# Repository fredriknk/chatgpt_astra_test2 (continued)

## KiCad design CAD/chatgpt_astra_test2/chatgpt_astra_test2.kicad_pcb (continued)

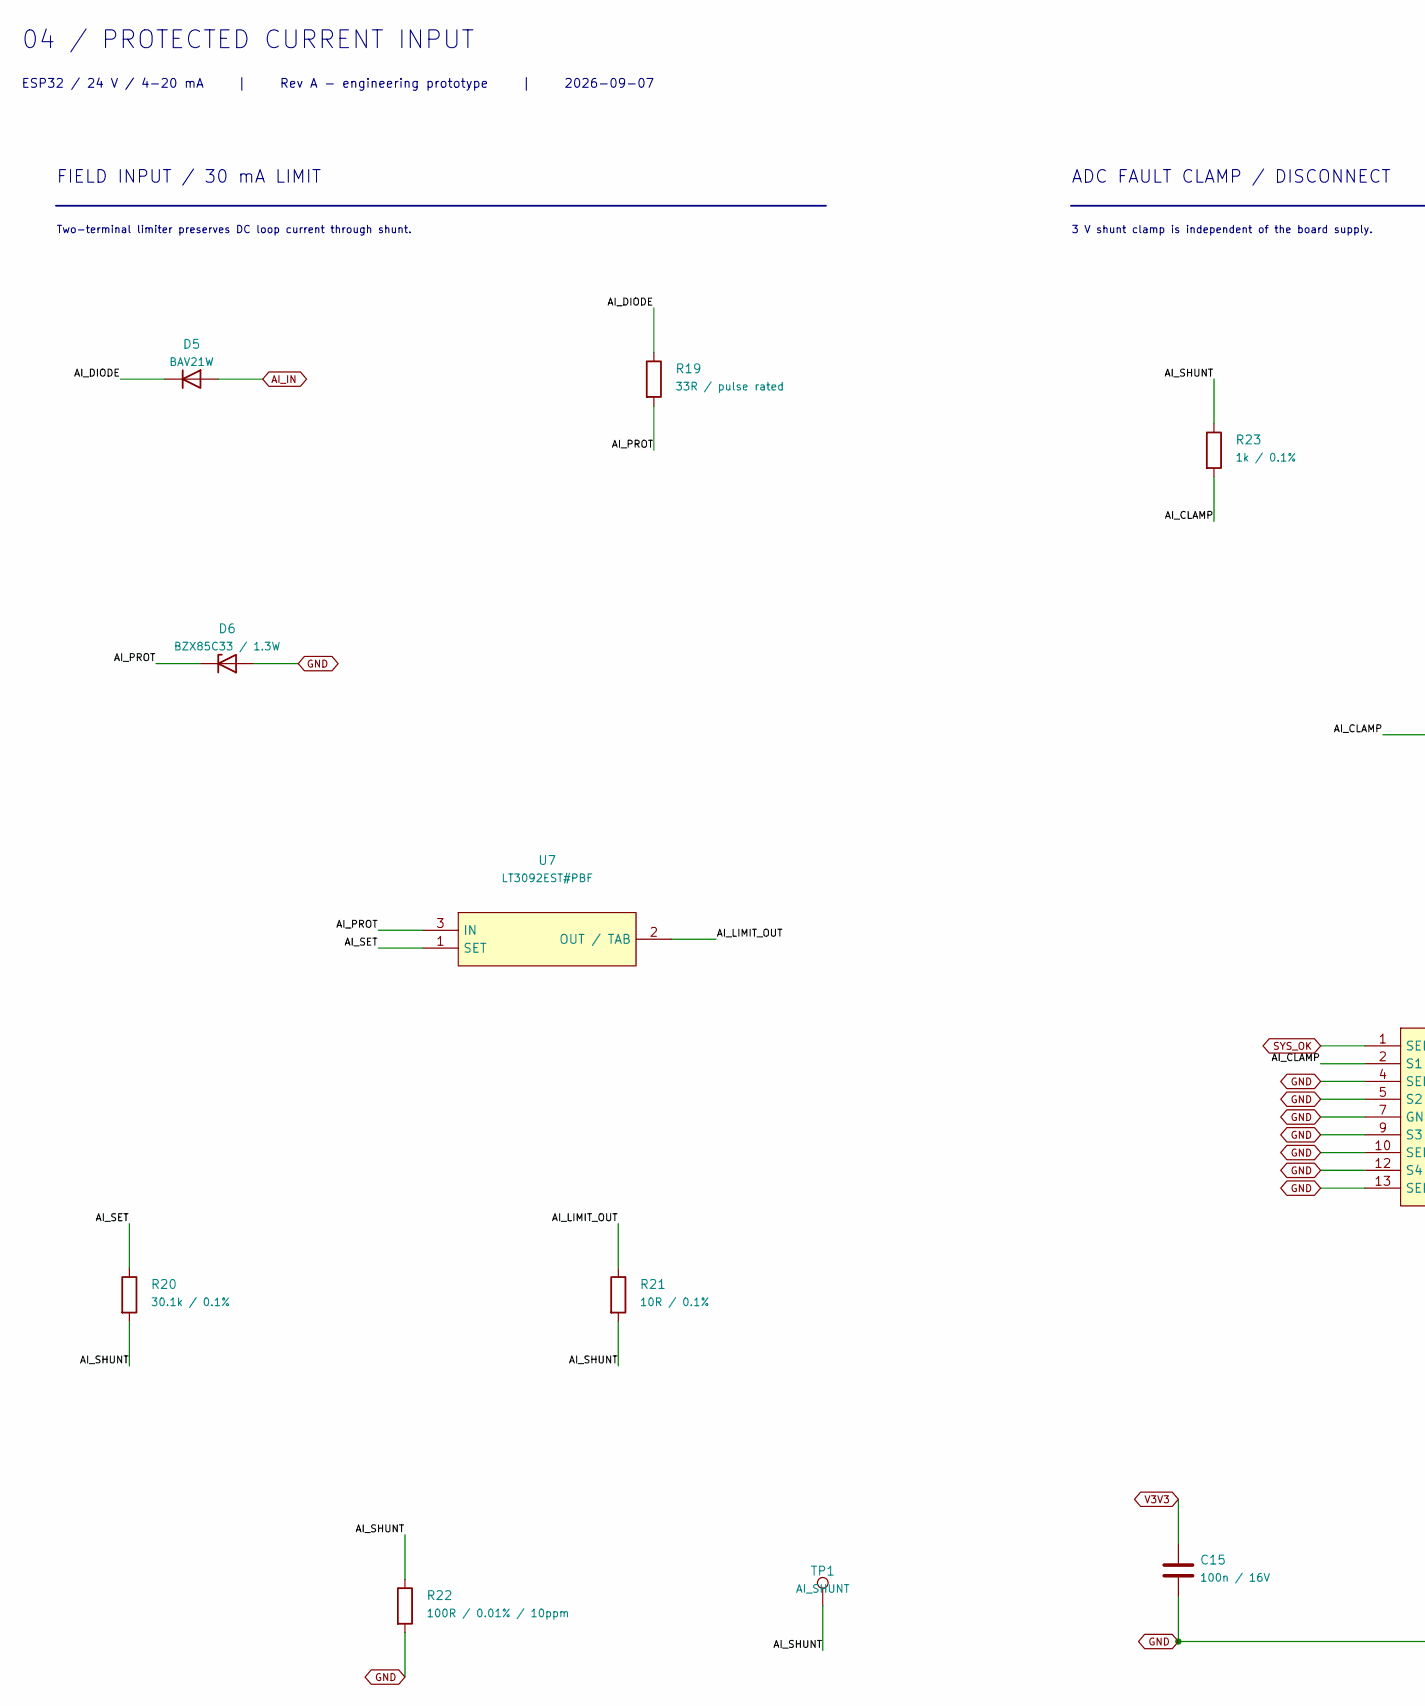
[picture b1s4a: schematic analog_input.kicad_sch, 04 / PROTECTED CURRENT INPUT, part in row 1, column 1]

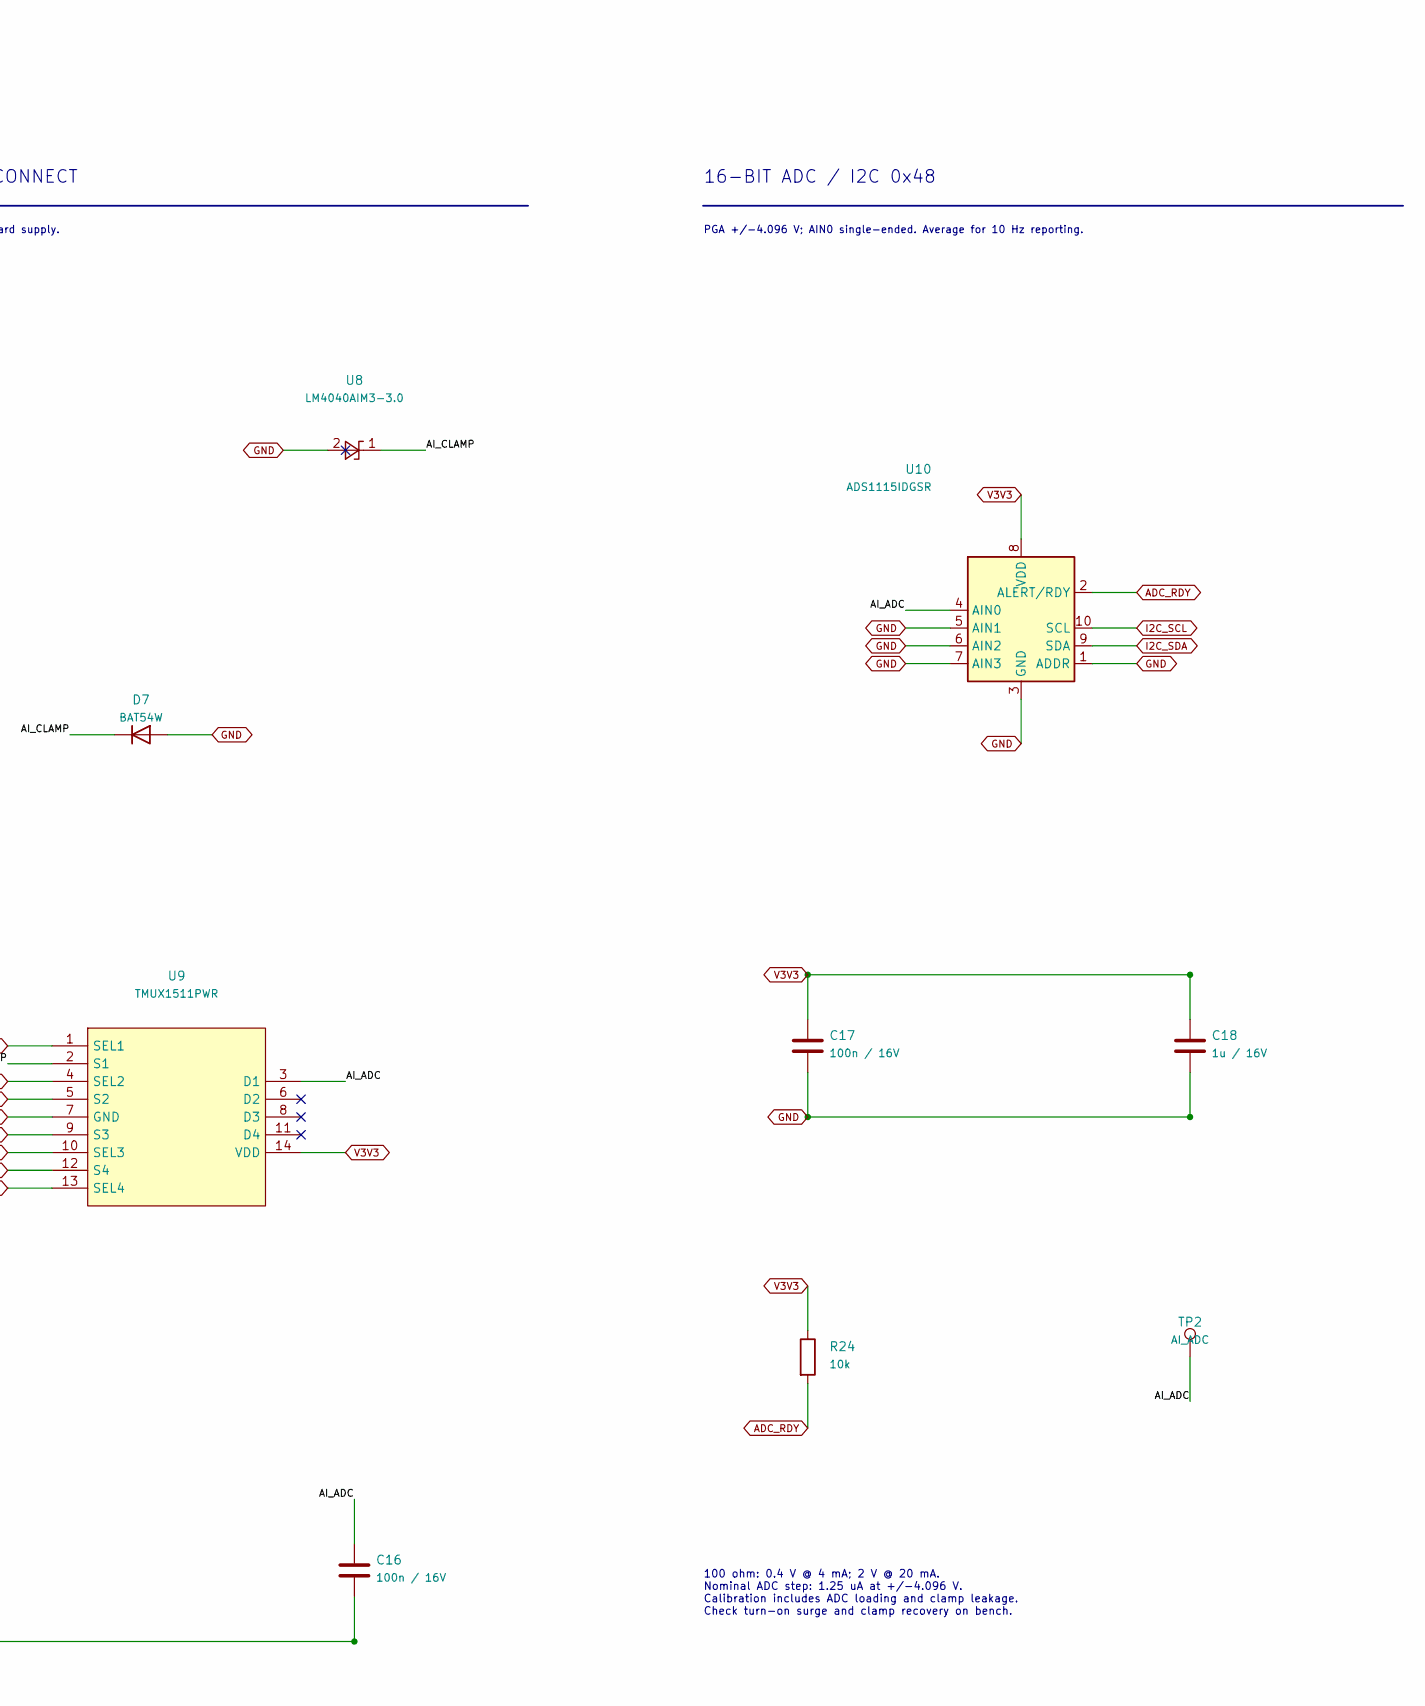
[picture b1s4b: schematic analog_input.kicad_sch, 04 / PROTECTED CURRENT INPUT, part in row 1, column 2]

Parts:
C15, C16, C17: 100n / 16V; C_0805_2012Metric
C18: 1u / 16V; C_0805_2012Metric
D5: BAV21W; D_SOD-123
D6: BZX85C33 / 1.3W; D_DO-41_SOD81_P10.16mm_Horizontal
D7: BAT54W; D_SOD-123
R19: 33R / pulse rated; R_1206_3216Metric
R20: 30.1k / 0.1%; R_0805_2012Metric
R21: 10R / 0.1%; R_0805_2012Metric
R22: 100R / 0.01% / 10ppm; R_1206_3216Metric
R23: 1k / 0.1%; R_0805_2012Metric
R24: 10k; R_0805_2012Metric
TP1: AI_SHUNT; TestPoint_Pad_D1.5mm
TP2: AI_ADC; TestPoint_Pad_D1.5mm
U7: LT3092EST#PBF; SOT-223-3_TabPin2
U8: LM4040AIM3-3.0; SOT-23
U9: TMUX1511PWR; TSSOP-14_4.4x5mm_P0.65mm
U10: ADS1115IDGSR; TSSOP-10_3x3mm_P0.5mm

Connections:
/04 / PROTECTED CURRENT INPUT/AI_ADC: C16.1, TP2.1, U9.3 (D1), U10.4 (AIN0)
/04 / PROTECTED CURRENT INPUT/AI_CLAMP: D7.1 (K), R23.2, U8.1 (K), U9.2 (S1)
/04 / PROTECTED CURRENT INPUT/AI_DIODE: D5.1 (K), R19.1
/04 / PROTECTED CURRENT INPUT/AI_LIMIT_OUT: R21.1, U7.2 (OUT / TAB)
/04 / PROTECTED CURRENT INPUT/AI_PROT: D6.1 (K), R19.2, U7.3 (IN)
/04 / PROTECTED CURRENT INPUT/AI_SET: R20.1, U7.1 (SET)
/04 / PROTECTED CURRENT INPUT/AI_SHUNT: R20.2, R21.2, R22.1, R23.1, TP1.1
ADC_RDY: R24.2, U10.2 (ALERT/RDY); also elsewhere on the board
AI_IN: D5.2 (A); also elsewhere on the board
GND: C15.2, C16.2, C17.2, C18.2, D6.2 (A), D7.2 (A), R22.2, U8.2 (A), U9.4 (SEL2), U9.5 (S2), U9.7 (GND), U9.9 (S3), U9.10 (SEL3), U9.12 (S4), U9.13 (SEL4), U10.1 (ADDR), U10.3 (GND), U10.5 (AIN1), U10.6 (AIN2), U10.7 (AIN3); also elsewhere on the board
I2C_SCL: U10.10 (SCL); also elsewhere on the board
I2C_SDA: U10.9 (SDA); also elsewhere on the board
SYS_OK: U9.1 (SEL1); also elsewhere on the board
V3V3: C15.1, C17.1, C18.1, R24.1, U9.14 (VDD), U10.8 (VDD); also elsewhere on the board

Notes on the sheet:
04 / PROTECTED CURRENT INPUT
ESP32 / 24 V / 4-20 mA | Rev A - engineering prototype | 2026-09-07
FIELD INPUT / 30 mA LIMIT
Two-terminal limiter preserves DC loop current through shunt.
ADC FAULT CLAMP / DISCONNECT
3 V shunt clamp is independent of the board supply.
16-BIT ADC / I2C 0x48
PGA +/-4.096 V; AIN0 single-ended. Average for 10 Hz reporting.
100 ohm: 0.4 V @ 4 mA; 2 V @ 20 mA. Nominal ADC step: 1.25 uA at +/-4.096 V. Calibration includes ADC loading and clamp leakage. Check turn-on surge and clamp recovery on bench.

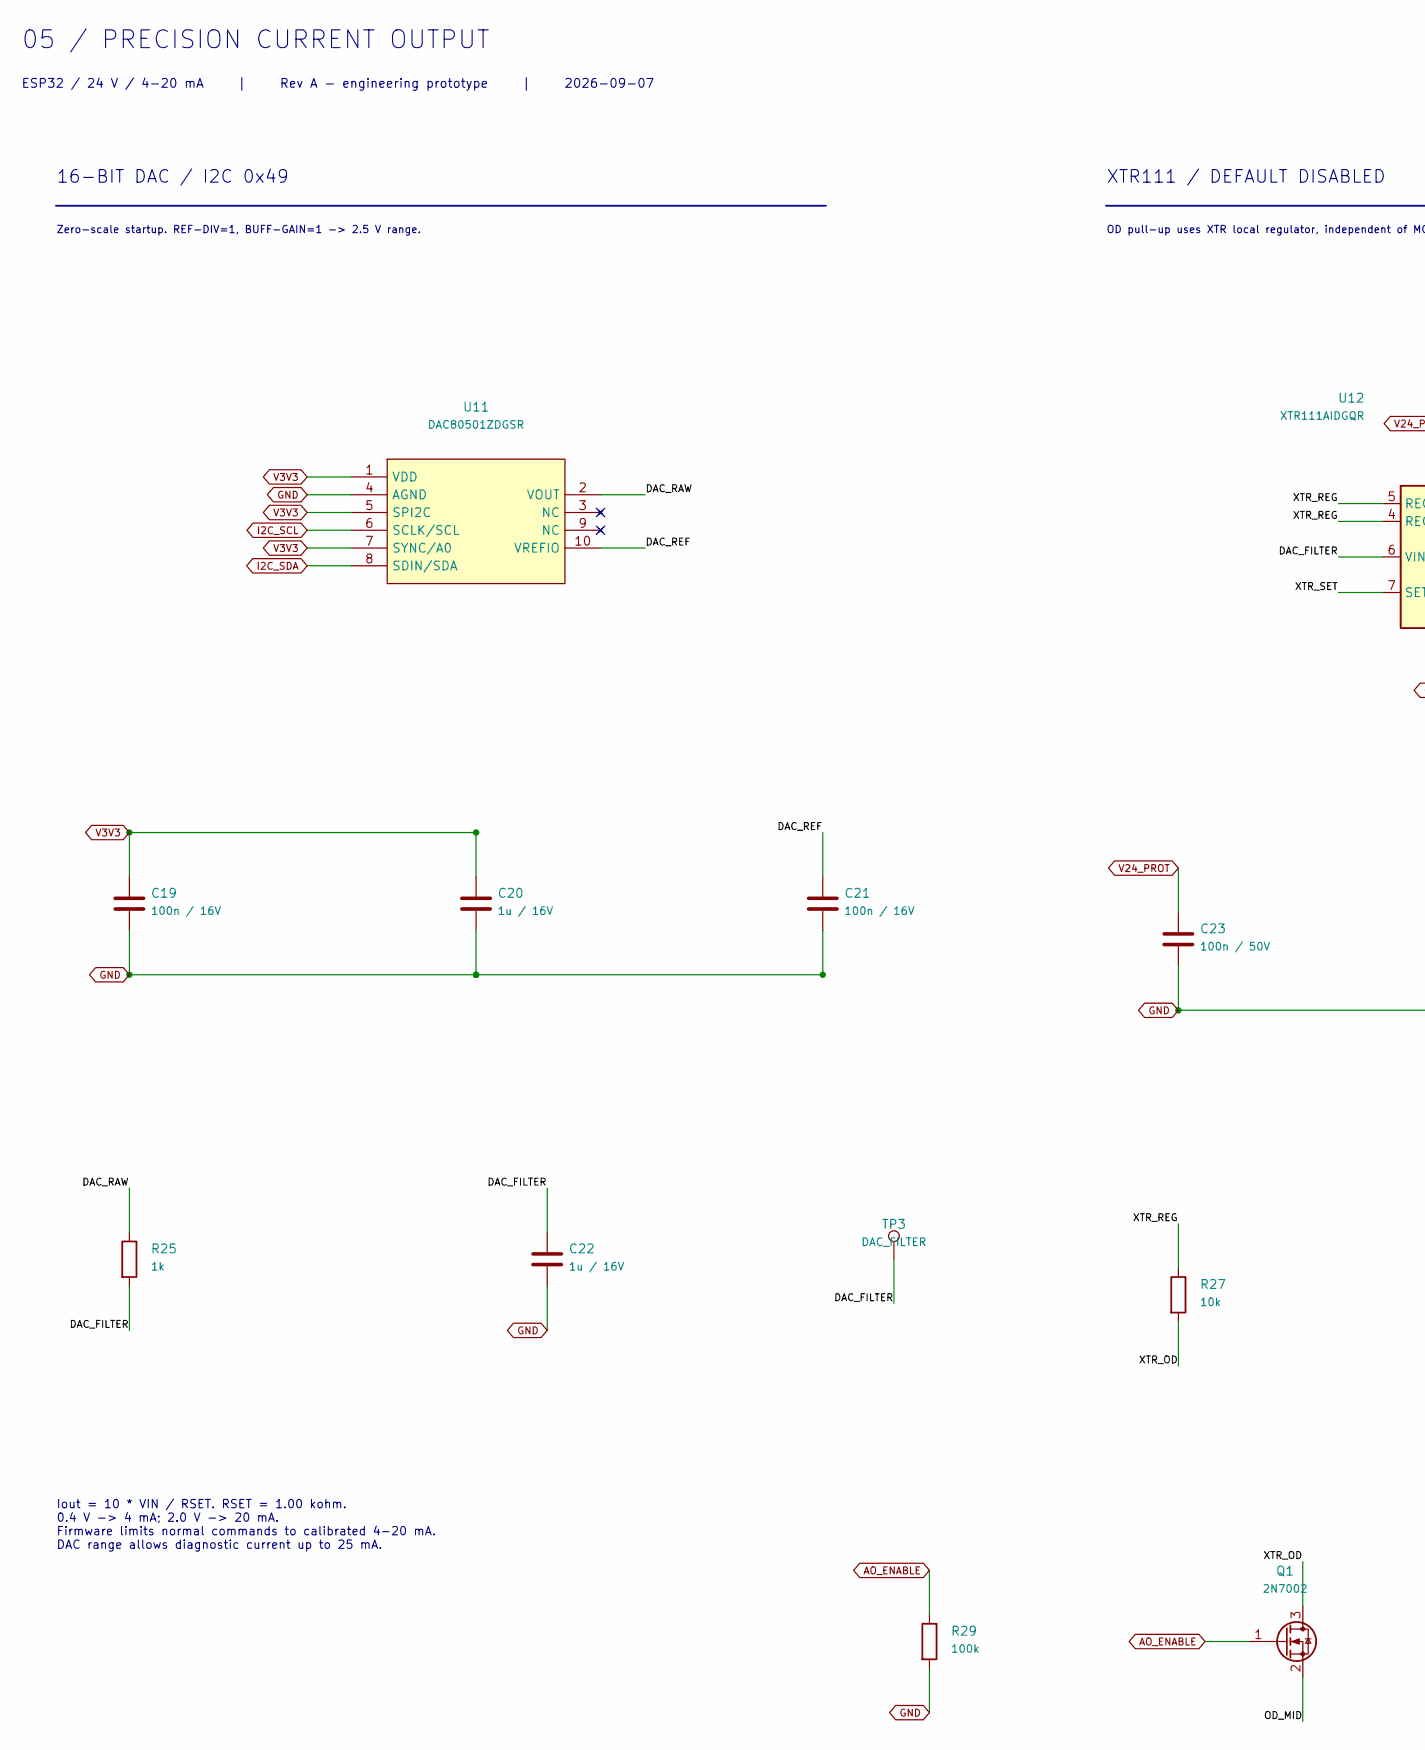
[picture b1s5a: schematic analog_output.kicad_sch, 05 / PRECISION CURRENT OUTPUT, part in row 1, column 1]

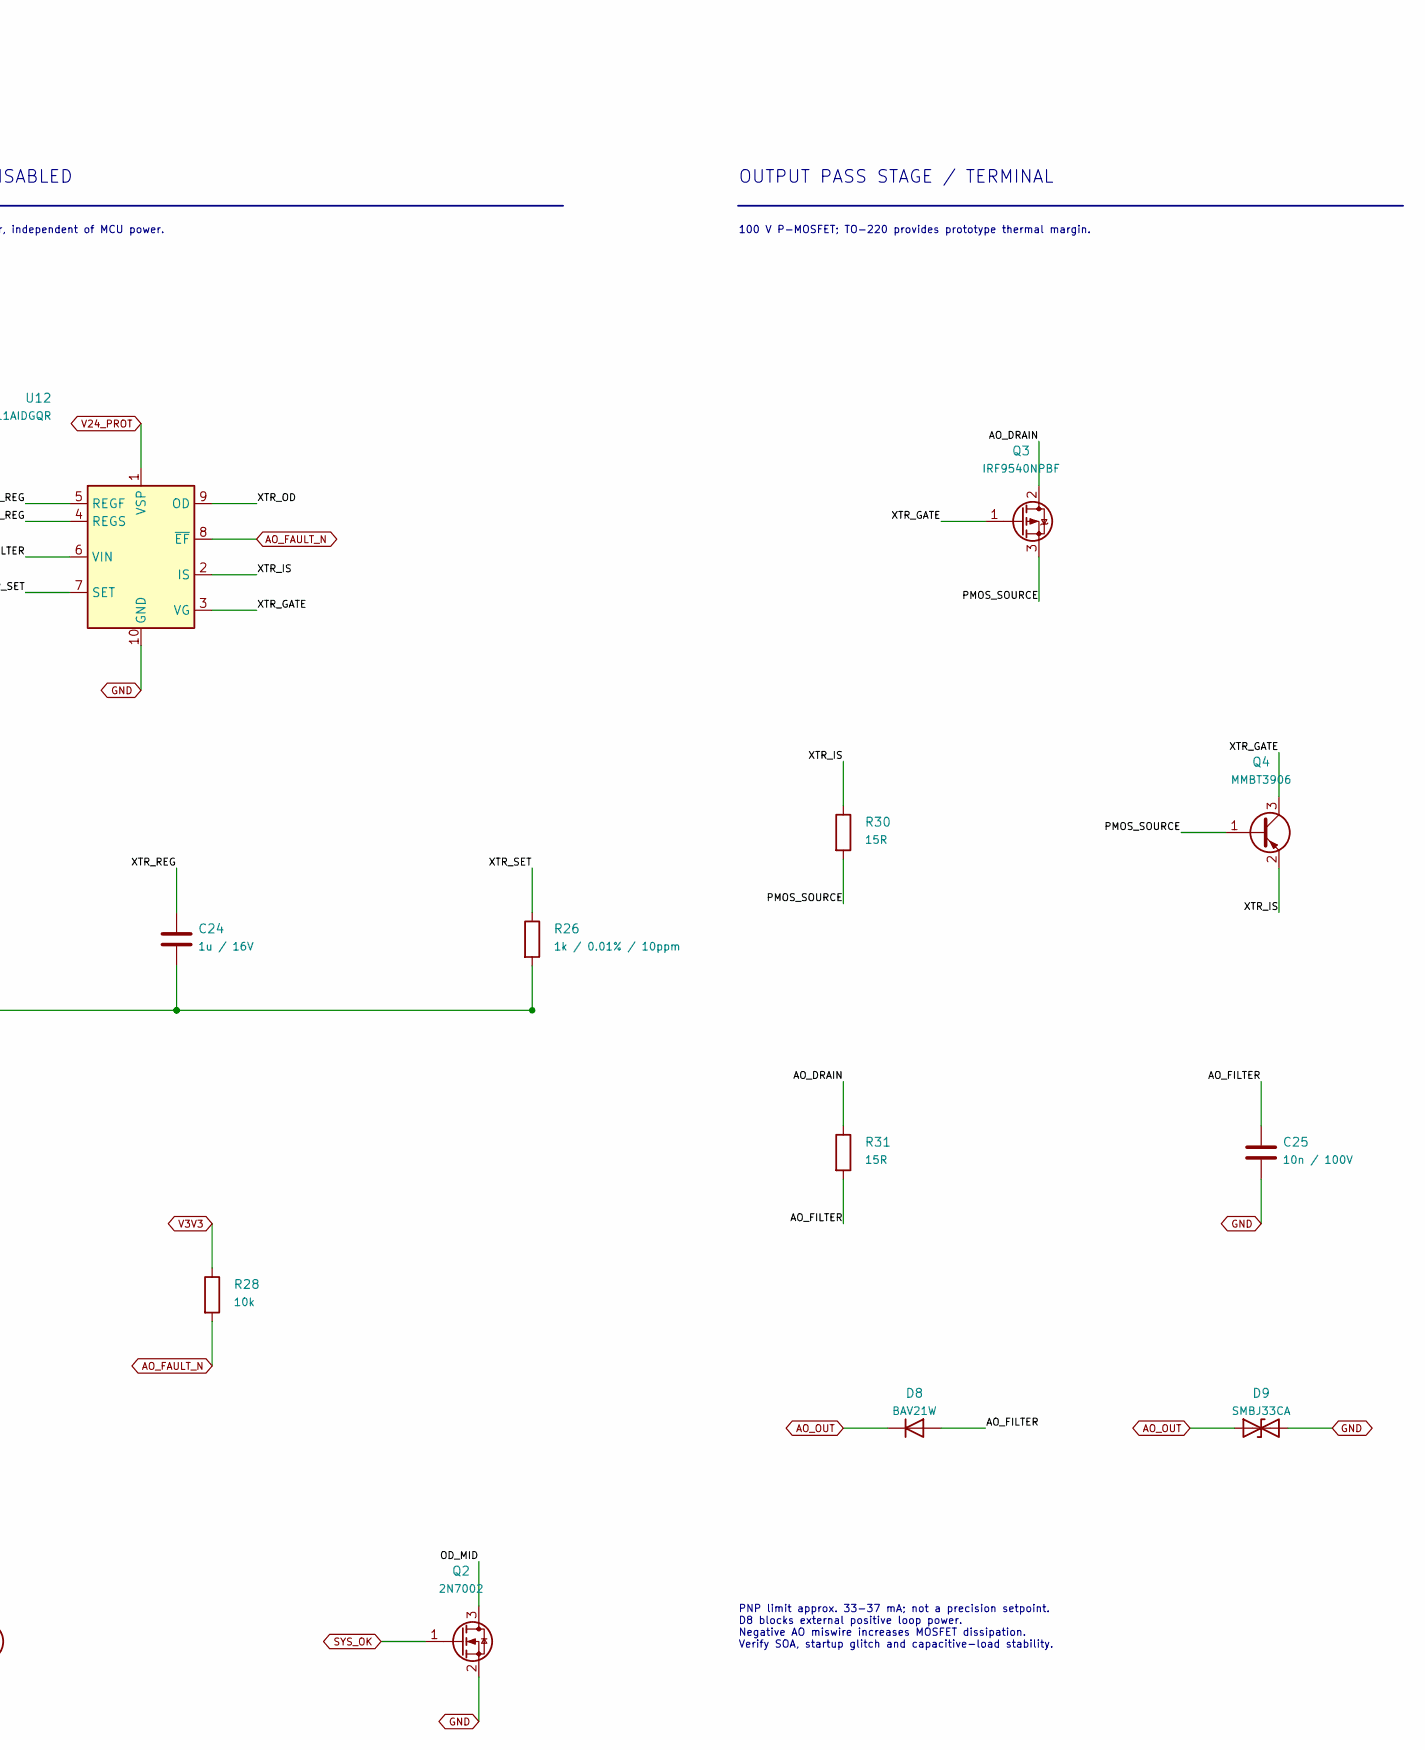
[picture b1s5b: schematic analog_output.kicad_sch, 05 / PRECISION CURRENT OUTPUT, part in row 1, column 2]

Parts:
C19, C21: 100n / 16V; C_0805_2012Metric
C20, C22, C24: 1u / 16V; C_0805_2012Metric
C23: 100n / 50V; C_0805_2012Metric
C25: 10n / 100V; C_0805_2012Metric
D8: BAV21W; D_SOD-123
D9: SMBJ33CA; D_SMB
Q1, Q2: 2N7002; SOT-23
Q3: IRF9540NPBF; TO-220-3_Vertical
Q4: MMBT3906; SOT-23
R25: 1k; R_0805_2012Metric
R26: 1k / 0.01% / 10ppm; R_0805_2012Metric
R27, R28: 10k; R_0805_2012Metric
R29: 100k; R_0805_2012Metric
R30, R31: 15R; R_0805_2012Metric
TP3: DAC_FILTER; TestPoint_Pad_D1.5mm
U11: DAC80501ZDGSR; VSSOP-10_3x3mm_P0.5mm
U12: XTR111AIDGQR; MSOP-10-1EP_3x3mm_P0.5mm_EP2.2x3.1mm_Mask1.83x1.89mm_Therma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

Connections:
/05 / PRECISION CURRENT OUTPUT/AO_DRAIN: Q3.2 (D), R31.1
/05 / PRECISION CURRENT OUTPUT/AO_FILTER: C25.1, D8.2 (A), R31.2
/05 / PRECISION CURRENT OUTPUT/DAC_FILTER: C22.1, R25.2, TP3.1, U12.6 (VIN)
/05 / PRECISION CURRENT OUTPUT/DAC_RAW: R25.1, U11.2 (VOUT)
/05 / PRECISION CURRENT OUTPUT/DAC_REF: C21.1, U11.10 (VREFIO)
/05 / PRECISION CURRENT OUTPUT/OD_MID: Q1.2 (S), Q2.3 (D)
/05 / PRECISION CURRENT OUTPUT/PMOS_SOURCE: Q3.3 (S), Q4.1 (B), R30.2
/05 / PRECISION CURRENT OUTPUT/XTR_GATE: Q3.1 (G), Q4.3 (C), U12.3 (VG)
/05 / PRECISION CURRENT OUTPUT/XTR_IS: Q4.2 (E), R30.1, U12.2 (IS)
/05 / PRECISION CURRENT OUTPUT/XTR_OD: Q1.3 (D), R27.2, U12.9 (OD)
/05 / PRECISION CURRENT OUTPUT/XTR_REG: C24.1, R27.1, U12.4 (REGS), U12.5 (REGF)
/05 / PRECISION CURRENT OUTPUT/XTR_SET: R26.1, U12.7 (SET)
AO_ENABLE: Q1.1 (G), R29.1; also elsewhere on the board
AO_FAULT_N: R28.2, U12.8 (~EF); also elsewhere on the board
AO_OUT: D8.1 (K), D9.1 (A1); also elsewhere on the board
GND: C19.2, C20.2, C21.2, C22.2, C23.2, C24.2, C25.2, D9.2 (A2), Q2.2 (S), R26.2, R29.2, U11.4 (AGND), U12.10 (GND), U12.11 (GND); also elsewhere on the board
I2C_SCL: U11.6 (SCLK/SCL); also elsewhere on the board
I2C_SDA: U11.8 (SDIN/SDA); also elsewhere on the board
SYS_OK: Q2.1 (G); also elsewhere on the board
V3V3: C19.1, C20.1, R28.1, U11.1 (VDD), U11.5 (SPI2C), U11.7 (SYNC/A0); also elsewhere on the board
V24_PROT: C23.1, U12.1 (VSP); also elsewhere on the board

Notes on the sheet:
05 / PRECISION CURRENT OUTPUT
ESP32 / 24 V / 4-20 mA | Rev A - engineering prototype | 2026-09-07
16-BIT DAC / I2C 0x49
Zero-scale startup. REF-DIV=1, BUFF-GAIN=1 -> 2.5 V range.
Iout = 10 * VIN / RSET. RSET = 1.00 kohm. 0.4 V -> 4 mA; 2.0 V -> 20 mA. Firmware limits normal commands to calibrated 4-20 mA. DAC range allows diagnostic current up to 25 mA.
XTR111 / DEFAULT DISABLED
OD pull-up uses XTR local regulator, independent of MCU power.
OUTPUT PASS STAGE / TERMINAL
100 V P-MOSFET; TO-220 provides prototype thermal margin.
PNP limit approx. 33-37 mA; not a precision setpoint. D8 blocks external positive loop power. Negative AO miswire increases MOSFET dissipation. Verify SOA, startup glitch and capacitive-load stability.

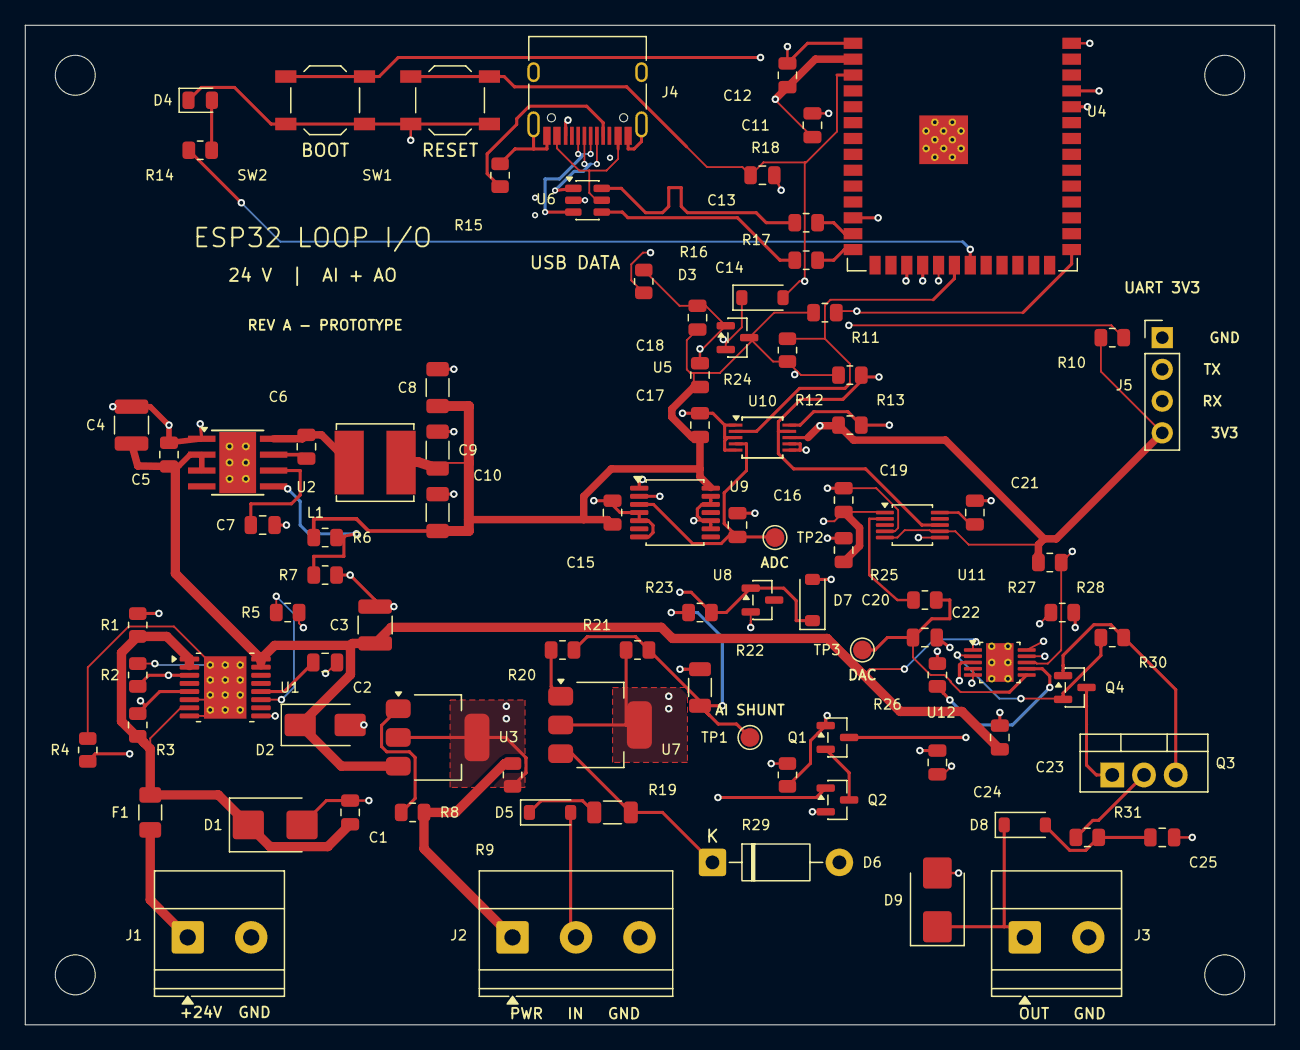
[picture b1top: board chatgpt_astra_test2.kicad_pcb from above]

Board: 4 copper layers, 100.0 x 80.0 mm, 97 parts (0 on the bottom side), 59 nets.

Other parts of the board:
H1, H2, H3, H4: M3 / 3.2mm; MountingHole_3.2mm_M3

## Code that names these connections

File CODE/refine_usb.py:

"""Manual USB pair routing; run once against the pre-USB refinement board.

Equivalent ESD channels are swapped in the matching schematic and intent.
The named fabrication stackup is documented separately; impedance needs fab control.
"""
from pathlib import Path
import json,re,sys
import pcbnew as p
import wx
wx.Log.EnableLogging(False)
root=Path(__file__).resolve().parents[1];base=root/'CAD/chatgpt_astra_test2/chatgpt_astra_test2';target=base.with_suffix('.kicad_pcb')
pro=json.loads(base.with_suffix('.kicad_pro').read_text())
for nc in pro['net_settings']['classes']:
    if nc['name']=='USB':nc.update(clearance=.15,track_width=.25,diff_pair_width=.25,diff_pair_gap=.15,via_diameter=.5,via_drill=.25)
pro['board']['design_settings']['rules'].update(min_via_diameter=.5,min_through_hole_diameter=.25)
base.with_suffix('.kicad_pro').write_text(json.dumps(pro,indent=2)+'\n')
mgr=p.GetSettingsManager();mgr.LoadProject(str(base.with_suffix('.kicad_pro')));b=p.LoadBoard(str(target))
remove=set()
copper_only='--copper-only' in sys.argv
for t in b.GetTracks():
    usb='USB_D' in t.GetNetname()
    points=[t.GetPosition()] if isinstance(t,p.PCB_VIA) else [t.GetStart(),t.GetEnd()]
    xs=[p.ToMM(a.x) for a in points];ys=[p.ToMM(a.y) for a in points]
    corridor=max(xs)>=92 and min(xs)<=116 and max(ys)>=60 and min(ys)<=78
    # Clear the local controller routing to accommodate relocated parts and pair.
    ground_return=t.GetNetname()=='GND' and ((isinstance(t,p.PCB_VIA) and (round(xs[0],2),round(ys[0],2)) in [(96.8,60.6),(90.8,63.8),(90.8,65.2),(94.8,64)]) or (not isinstance(t,p.PCB_VIA) and abs(xs[0]-93.8625)<.001 and abs(ys[0]-64)<.001))
    if usb or (corridor and not copper_only) or ground_return:remove.add(t.m_Uuid.AsString())
s=target.read_text();target.write_text(re.sub(r'\n\t\((?:segment|via)\n.*?\n\t\)',lambda m:'' if any(u in m[0] for u in remove) else m[0],s,flags=re.S))
b=p.LoadBoard(str(target));fps={f.GetReference():f for f in b.GetFootprints()}
def xy(x,y):return p.VECTOR2I(p.FromMM(x),p.FromMM(y))
def pad(r,n):return next(a for a in fps[r].Pads() if a.GetNumber()==str(n))
for ref,x,y in [('R18',112.5,65.8),('R17',112.5,68.8),('U5',107,75),('C14',103.8,73.4),('D3',109,71.8),('R10',137,75),('R16',99.5,70.5)]:
    f=fps[ref];f.SetPosition(xy(x,y))
    if ref=='R10':f.SetOrientationDegrees(0)
prefix='/03 / ESP32 AND USB/'
for pin,name in [('1','USB_DM'),('6','USB_DM_ESD'),('3','USB_DP'),('4','USB_DP_ESD')]:pad('U6',pin).SetNet(b.FindNet(prefix+name))
def path(net,pts,layer=p.F_Cu,width=.25):
    pts=[xy(*a) if isinstance(a,tuple) else a for a in pts]
    for a,z in zip(pts,pts[1:]):
        t=p.PCB_TRACK(b);t.SetStart(a);t.SetEnd(z);t.SetLayer(layer);t.SetWidth(p.FromMM(width));t.SetNetCode(net);b.Add(t)
def via(net,x,y):
    v=p.PCB_VIA(b);v.SetPosition(xy(x,y));v.SetWidth(p.FromMM(.5));v.SetDrill(p.FromMM(.25));v.SetViaType(p.VIATYPE_THROUGH);v.SetLayerPair(p.F_Cu,p.B_Cu);v.SetNetCode(net);b.Add(v)
def route(a,z,pts=(),width=.25):
    a=pad(*a);z=pad(*z);assert a.GetNetCode()==z.GetNetCode();path(a.GetNetCode(),[a.GetPosition(),*pts,z.GetPosition()],width=width)
# Paired protected trunk, with series resistors near the module.
route(('U6',6),('R18',1),[(97.7,63.05),(99.65,65),(101,65),(101.5,64.5),(101.5,62.9945),(102.5,62.9945),(102.5,64.5),(103,65),(108.5,65),(109.3,65.8)])
route(('U6',4),('R17',1),[(97.7843,64.95),(98.2343,65.4),(107,65.4),(110.4,68.8)])
route(('R18',2),('U4',13),[(114.7,65.8),(115.58,66.68)])
route(('R17',2),('U4',14),[(114.7,68.8),(115.55,67.95)])
# USB-C duplicate data contacts join at symmetric midpoints on B.Cu.
for name,pins,xs,y in [('USB_DP',['B6','A6'],[94.25,95.25],60.3),('USB_DM',['A7','B7'],[94.75,95.75],61.1)]:
    net=b.FindNet(prefix+name).GetNetCode()
    for pin,x in zip(pins,xs):path(net,[pad('J4',pin).GetPosition(),(x,y)],width=.15);via(net,x,y)
    middle=(sum(xs)/2,y);path(net,[(xs[0],y),middle,(xs[1],y)],p.B_Cu,.15)
    if name=='USB_DP':
        path(net,[middle,(92.75,62.3),(91.6,62.3),(91.6,64.95)],p.B_Cu);via(net,91.6,64.95);path(net,[(91.6,64.95),pad('U6',3).GetPosition()])
    else:
        path(net,[middle,(94.65,61.7),(93.925,61.7),(92.4,63.225)],p.B_Cu);via(net,92.4,63.225);path(net,[(92.4,63.225),pad('U6',1).GetPosition()])
# Ground returns beside the crossover transitions and ESD reference pin.
g=b.FindNet('GND').GetNetCode()
for x,y in [(96.8,60.6),(90.8,63.8),(90.8,65.2),(94.8,64)]:via(g,x,y)
path(g,[pad('U6',2).GetPosition(),(94.8,64)])
z=p.ZONE(b);z.SetNet(b.FindNet('GND'));z.SetLayer(p.In2_Cu);z.SetLocalClearance(p.FromMM(.2));z.SetMinThickness(p.FromMM(.2));z.SetPadConnection(p.ZONE_CONNECTION_FULL)
poly=z.Outline();poly.NewOutline()
for x,y in [(90.5,59.8),(98,59.8),(98,66),(90.5,66)]:v=xy(x,y);poly.Append(v.x,v.y)
if not copper_only:b.Add(z)
from build_board import place_references
place_references(b,{r:f for r,f in fps.items() if not r.startswith('H')})
b.BuildConnectivity();p.ZONE_FILLER(b).Fill(b.Zones());p.SaveBoard(str(target),b);mgr.UnloadProject(b.GetProject(),False)

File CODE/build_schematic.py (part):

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    c(mcu,'C14',180,125,'100n / 16V','V3V3');r(mcu,'R12',225,125,'4.7k','V3V3','I2C_SDA');r(mcu,'R13',275,125,'4.7k','V3V3','I2C_SCL')
    r(mcu,'R14',180,170,'1k','LED_STATUS','LED_A')
    mcu.add('D4',key('Device','LED'),230,170,{'1':'GND','2':'LED_A'},'GREEN','LED_SMD:LED_0805_2012Metric')
    mcu.add('J5',key('Connector_Generic','Conn_01x04'),280,210,{'1':'GND','2':'UART_TX','3':'UART_RX','4':'V3V3'},'UART / 3.3 V ONLY','Connector_PinHeader_2.54mm:PinHeader_1x04_P2.54mm_Vertical')
    mcu.note(170,240,'I2C: ADS1115 0x48; DAC80501 0x49 (A0 tied to VDD).\nBOOT held low during RESET enters ROM download mode.\nSYS_OK is supply supervision, not a firmware watchdog.',1.1)
    mcu.section(310,35,'USB-C / DATA ONLY','No VBUS-to-board power connection.')
    uc=key('Connector','USB_C_Receptacle_USB2.0_16P');un={num:None for num,*_ in pins(SYMS[uc])}
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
